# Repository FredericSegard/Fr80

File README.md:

# Fr80

 ## Z80 Homebrew computer, code-named Fr80, pronounced Freddy.
This repo will contain all the elements for a complete Z80 system (Work in progress)

### The Backplane:
The goal is to first make a ubiquitous backplane that could accommodate many 8 or 16-bit architectures, including most x86 that is compatible, Z80, eZ80, z8000, 65C02, 65C816, 6809... You name it, it should handle it. The only difference is in the PCB labeling. I have labeled the breadboard header as per the PC ISA standard on row 1, row 2 is for the Z80, and row 3 is for the 65C02. The breadboard pins are pin-to-pin mapped A1-A13 on the left, and B1-B31 on the right.
 
This backplane follows the ISA power rail standard. This means the +5, ground, +12V, and -12V lanes are where they should be. However, there is provision for a -5V regulator, since most ATX PSUs no longer support it. And since 3.3V is more prevalent these days, I have assigned the -5V lane to +3.3V. However, you can select which voltage you need by simply changing a jumper's position. There is an alternate barrel jack power input for 5 volts only. There is a provision for a 3.3V regulator should you need it. Both power sources are soft power-on. Jumpers are present to repurpose the button, since electrically, they could not be tied together.

It is a passive backplane, so there should be no interference with other signal types. So in theory, you could reassign all non-power rail buses, except for the reset lane and A7 and A8. The reset circuit, which is jumper selectable between active high or active low, cannot be reassigned. And the CPU activity LED, which monitors A7 or A8 (jumper selectable), can't also be moved.

I have just received the PCBs from the fab house. I will assemble it and let you know if everything works as intended.

.jpg?raw=true)

### The Core CPU card:
I made several iterations of the CPU board, but now I'm satisfied with this revision 3. It's a very compact 100mm² 4-layer board, that contains the CPU, 128KB Flash, 512KM RAM, bank switching circuitry, a priority interrupt encoder, a CTC, and an SIO with USB ports (type A and type B).

I gave myself a challenge to fit as much as possible in a 100mm² PCB, all the while managing to put in a ZIF socket and some blinkenlights. The board is so stuffed with components, that I needed to place the bypass capacitors in the sockets, as well as some resistors. 

I will send out the Gerber for manufacturing, and keep you posted.

/Docs%20and%20Images/Front%20with%20components.jpg?raw=true)

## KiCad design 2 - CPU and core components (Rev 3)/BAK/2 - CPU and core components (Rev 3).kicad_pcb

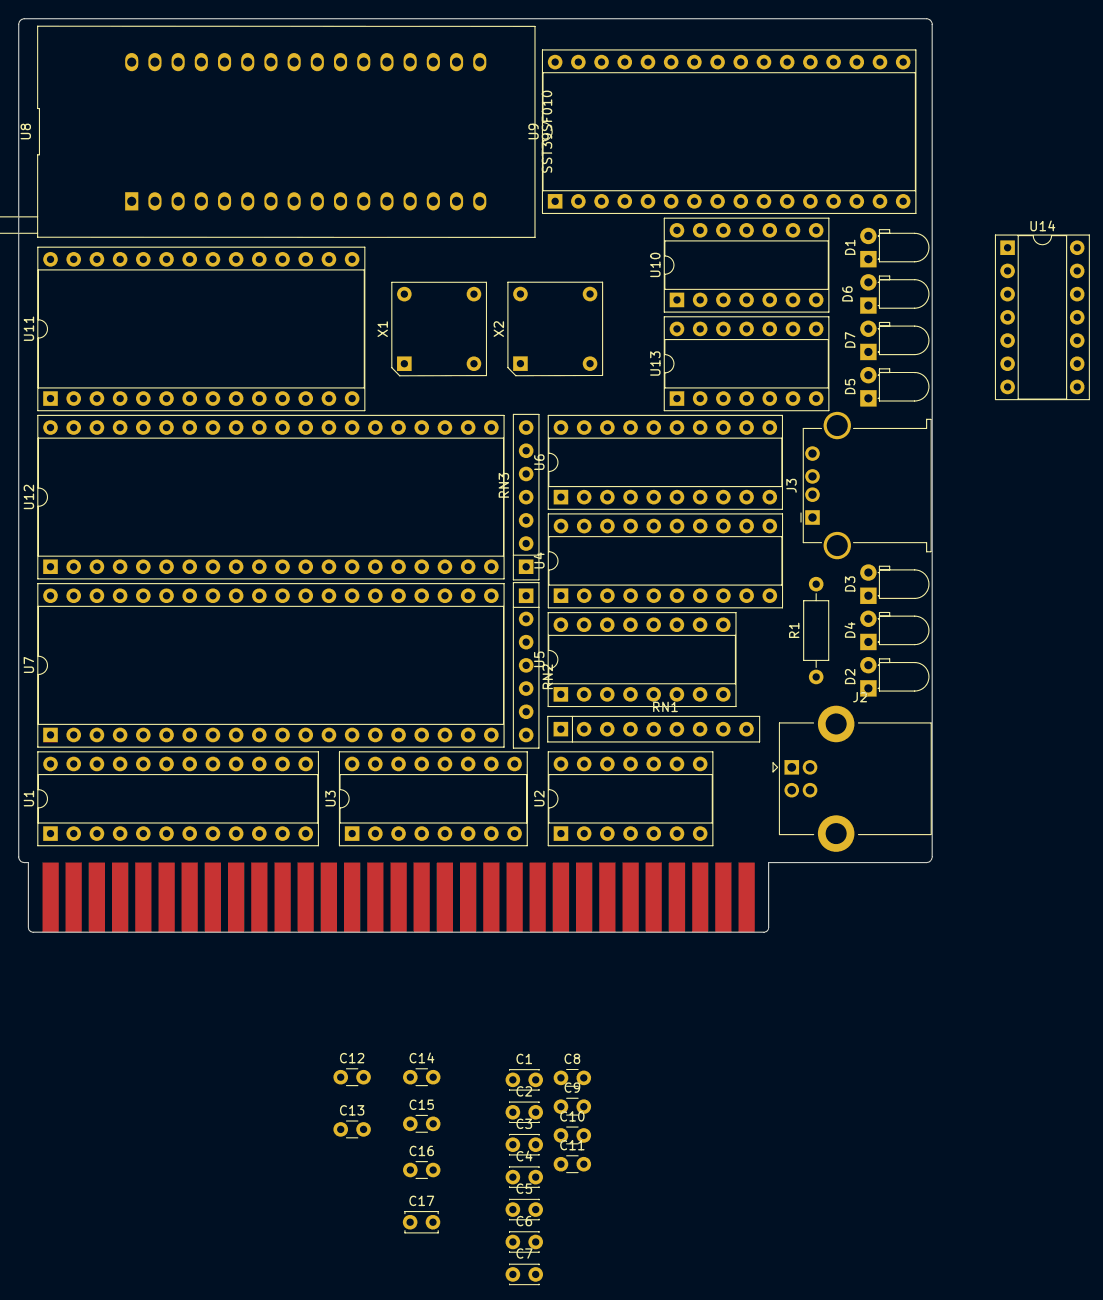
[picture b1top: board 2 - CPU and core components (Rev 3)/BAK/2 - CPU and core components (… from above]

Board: 2 copper layers, 100.0 x 100.0 mm, 47 parts (0 on the bottom side), 95 nets, no tracks yet.

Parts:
C1, C2, C3, C4, C5, C6, C7: 1µF; C_Disc_D3.0mm_W2.0mm_P2.50mm
C8, C9, C10, C11, C14, C15, C16: 1µF; C_Disc_D3.0mm_W1.6mm_P2.50mm
C12, C13: 0.47µF; C_Disc_D3.0mm_W1.6mm_P2.50mm
C17: 1µF; C_Disc_D3.4mm_W2.1mm_P2.50mm
D1: STATUS; LED_D3.0mm_Horizontal_O1.27mm_Z2.0mm
D2: USB 1; LED_D3.0mm_Horizontal_O1.27mm_Z2.0mm
D3: TX 1; LED_D3.0mm_Horizontal_O1.27mm_Z2.0mm
D4: RX 1; LED_D3.0mm_Horizontal_O1.27mm_Z2.0mm
D5: USB 2; LED_D3.0mm_Horizontal_O1.27mm_Z2.0mm
D6: TX 2; LED_D3.0mm_Horizontal_O1.27mm_Z2.0mm
D7: RX 2; LED_D3.0mm_Horizontal_O1.27mm_Z2.0mm
J1: CARD EDGE; BUS_XT v2
J2: COM 1; USB_B_Lumberg_2411_02_Horizontal
J3: COM 2; USB_A_Stewart_SS-52100-001_Horizontal
R1: 3K3; R_Axial_DIN0207_L6.3mm_D2.5mm_P10.16mm_Horizontal
RN1: 3K3; R_Array_SIP9
RN2, RN3: 3K3; R_Array_SIP7
U1: ATF22V10C; DIP-24_W7.62mm_Socket
U2: 74HCT32; DIP-14_W7.62mm_Socket
U3: 74LS174; DIP-16_W7.62mm_Socket
U4: 74HCT541; DIP-20_W7.62mm_Socket
U5: 74HCT148; DIP-16_W7.62mm_Socket
U6: 74HCT573; DIP-20_W7.62mm_Socket
U7: Z84C0010; DIP-40_W15.24mm_Socket
U8: SST39SF010; ZIF_Socket-32
U9: AS6C4008; DIP-32_W15.24mm_Socket
U10: 74HCT30; DIP-14_W7.62mm_Socket
U11: Z84C3010; DIP-28_W15.24mm_Socket
U12: Z84C4010; DIP-40_W15.24mm_Socket
U13, U14: MCP2221A; DIP-14_W7.62mm_Socket
X1: 10 MHz; DIP-8-4_W7.62mm_Oscillator_Socket
X2: 3.6864 MHz; DIP-8-4_W7.62mm_Oscillator_Socket

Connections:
+5V: C1.1, C2.1, C3.1, C4.1, C5.1, C6.1, C7.1, C8.1, C9.1, C10.1, C11.1, C14.1, C15.1, C16.1, C17.1, J1.34 (B3), J1.60 (B29), RN1.1 (common), RN2.1 (common), RN3.1 (common), U1.24 (VCC), U2.14 (VCC), U3.16 (VCC), U4.20 (VCC), U5.16 (VCC), U6.20 (VCC), U7.11 (VCC), U8.32 (VCC), U9.32 (VCC), U10.14 (VCC), U11.24 (VCC), U12.9 (VCC), U13.1 (VCC), U14.1 (VCC), X1.1 (EN), X1.8 (Vcc), X2.1 (EN), X2.8 (Vcc)
/CTC & SIO/D1+: J2.3 (D+), U13.13 (D+)
/CTC & SIO/D1-: J2.2 (D-), U13.12 (D-)
/CTC & SIO/D2+: J3.3 (D+), U14.13 (D+)
/CTC & SIO/D2-: J3.2 (D-), U14.12 (D-)
/GND: J1.32 (B1), J1.41 (B10), J1.62 (B31)
/Glue Logic/RBA15: U2.2, U3.2 (Q0), U4.2 (A0)
/Glue Logic/RBA16: U2.5, U3.5 (Q1), U4.3 (A1)
/Glue Logic/RBA17: U2.10, U3.7 (Q2), U4.4 (A2)
/Glue Logic/RBA18: U2.13, U3.10 (Q3), U4.5 (A3)
A0: J1.31 (A31), U7.30 (A0), U8.12 (A0), U9.12 (A0), U11.18 (CS0), U12.34 (B/~A)
A1: J1.30 (A30), U7.31 (A1), U8.11 (A1), U9.11 (A1), U11.19 (CS1), U12.33 (C/~D)
A2: J1.29 (A29), U1.7 (I), U7.32 (A2), U8.10 (A2), U9.10 (A2)
A3: J1.28 (A28), U1.8 (I), U7.33 (A3), U8.9 (A3), U9.9 (A3)
A4: J1.27 (A27), U1.9 (I), U7.34 (A4), U8.8 (A4), U9.8 (A4)
A5: J1.26 (A26), U1.10 (I), U7.35 (A5), U8.7 (A5), U9.7 (A5)
A6: J1.25 (A25), U1.11 (I), U7.36 (A6), U8.6 (A6), U9.6 (A6)
A7: J1.24 (A24), U1.13 (I), U7.37 (A7), U8.5 (A7), U9.5 (A7)
A8: J1.23 (A23), U7.38 (A8), U8.27 (A8), U9.27 (A8)
A9: J1.22 (A22), U7.39 (A9), U8.26 (A9), U9.26 (A9)
A10: J1.21 (A21), U7.40 (A10), U8.23 (A10), U9.23 (A10)
A11: J1.20 (A20), U7.1 (A11), U8.25 (A11), U9.25 (A11)
A12: J1.19 (A19), U7.2 (A12), U8.4 (A12), U9.4 (A12)
A13: J1.18 (A18), U7.3 (A13), U8.28 (A13), U9.28 (A13)
A14: J1.17 (A17), U7.4 (A14), U8.29 (A14), U9.3 (A14)
A15: J1.16 (A16), U2.1, U2.4, U2.9, U2.12, U7.5 (A15), U8.3 (A15)
BA15: U2.3, U9.31 (A15)
BA16: U2.6, U9.2 (A16)
BA17: U2.8, U9.30 (A17)
BA18: U2.11, U9.1 (A18)
BUS_IEO: J1.15 (A15), RN2.6 (R5), U12.6 (IEI)
CLK: J1.51 (B20), U7.6 (CLK), U11.15 (CLK), U12.20 (CLK), X1.5 (OUT)
CLK2: J1.39 (B8), U11.21 (CLK/TRG2), U11.22 (CLK/TRG1), U11.23 (CLK/TRG0), U12.13 (~RxCA), U12.14 (~TxCA), U12.27 (~RxTxCB), X2.5 (OUT)
CTCLK: J1.14 (A14), U11.8 (ZC/TO1)
CTC_IEI: RN2.7 (R6), U11.13 (IEI), U12.7 (IEO)
D0: J1.9 (A9), U3.3 (D0), U4.18 (Y0), U6.19 (Q0), U7.14 (D0), U8.13 (DQ0), U9.13 (DQ0), U11.25 (D0), U12.40 (D0)
D1: J1.8 (A8), U3.4 (D1), U4.17 (Y1), U6.18 (Q1), U7.15 (D1), U8.14 (DQ1), U9.14 (DQ1), U11.26 (D1), U12.1 (D1)
D2: J1.7 (A7), U3.6 (D2), U4.16 (Y2), U6.17 (Q2), U7.12 (D2), U8.15 (DQ2), U9.15 (DQ2), U11.27 (D2), U12.39 (D2)
D3: J1.6 (A6), U3.11 (D3), U4.15 (Y3), U6.16 (Q3), U7.8 (D3), U8.17 (DQ3), U9.17 (DQ3), U11.28 (D3), U12.2 (D3)
D4: J1.5 (A5), U4.14 (Y4), U6.15 (Q4), U7.7 (D4), U8.18 (DQ4), U9.18 (DQ4), U11.1 (D4), U12.38 (D4)
D5: J1.4 (A4), U4.13 (Y5), U6.14 (Q5), U7.9 (D5), U8.19 (DQ5), U9.19 (DQ5), U11.2 (D5), U12.3 (D5)
D6: J1.3 (A3), U4.12 (Y6), U6.13 (Q6), U7.10 (D6), U8.20 (DQ6), U9.20 (DQ6), U11.3 (D6), U12.37 (D6)
D7: J1.2 (A2), U4.11 (Y7), U6.12 (Q7), U7.13 (D7), U8.21 (DQ7), U9.21 (DQ7), U11.4 (D7), U12.4 (D7)
GND: C1.2, C2.2, C3.2, C4.2, C5.2, C6.2, C7.2, C8.2, C9.2, C10.2, C11.2, C12.2, C13.2, C14.2, C15.2, C16.2, C17.2, D1.1 (K), J2.4 (GND), J2.5 (Shield), J3.4 (GND), J3.5 (Shield), U1.12 (GND), U2.7 (GND), U3.8 (GND), U3.13 (D4), U3.14 (D5), U4.6 (A4), U4.7 (A5), U4.8 (A6), U4.9 (A7), U4.10 (GND), U5.5 (EI), U5.8 (GND), U6.2 (D0), U6.6 (D4), U6.7 (D5), U6.8 (D6), U6.9 (D7), U6.10 (GND), U7.29 (GND), U8.1 (NC), U8.2 (A16), U8.16 (GND), U8.30 (NC), U9.16 (GND), U10.7 (GND), U11.5 (GND), U12.18 (~CTSA), U12.19 (~DCDA), U12.22 (~DCDB), U12.23 (~CTSB), U12.31 (GND), U13.14 (GND), U14.14 (GND), X1.4 (GND), X2.4 (GND)
MODE2: U1.14 (I/O), U6.1 (OE)
unnamed: D1.2 (A), R1.2
unnamed: D2.2 (A), RN3.4 (R3)
unnamed: D2.1 (K), U13.7 (GP2_(USB))
unnamed: D3.2 (A), RN3.3 (R2)
unnamed: D3.1 (K), U13.3 (GP1_(Tx))
unnamed: D4.2 (A), RN3.2 (R1)
unnamed: D4.1 (K), U13.2 (GP0_(Rx))
unnamed: D5.2 (A), RN3.5 (R4)
unnamed: D5.1 (K), U14.7 (GP2_(USB))
unnamed: D6.2 (A), RN3.6 (R5)
unnamed: D6.1 (K), U14.3 (GP1_(Tx))
unnamed: D7.2 (A), RN3.7 (R6)
unnamed: D7.1 (K), U14.2 (GP0_(Rx))
unnamed: R1.1, U10.8
unnamed: U5.9 (S0), U6.3 (D1)
unnamed: U5.7 (S1), U6.4 (D2)
unnamed: U5.6 (S2), U6.5 (D3)
unnamed: U11.7 (ZC/TO0), U11.20 (CLK/TRG3)
unnamed: U12.12 (RxDA), U13.6 (Tx_Out)
unnamed: U12.28 (RxDB), U14.6 (Tx_Out)
unnamed: U12.15 (TxDA), U13.5 (Rx_In)
unnamed: U12.26 (TxDB), U14.5 (Rx_In)
unnamed: C12.1, U13.11 (VUSB)
unnamed: C13.1, U14.11 (VUSB)
~BANK_RD: U1.17 (I/O), U4.1 (G1), U4.19 (G2)
~BANK_WR: U1.18 (I/O), U3.9 (Cp)
~BUSAK: J1.48 (B17), U7.23 (~BUSAK), U10.11
~BUSRQ: J1.47 (B16), RN2.2 (R1), U7.25 (~BUSRQ), U10.6
~CTC_CS: U1.15 (I/O), U11.16 (~CE)
~HALT: J1.50 (B19), U7.18 (~HALT), U10.2
~INT: RN2.3 (R2), U5.14 (GS), U7.16 (~INT), U10.4
~IORQ: J1.43 (B12), U1.3 (I), U7.20 (~IORQ), U11.10 (~IORQ), U12.36 (~IORQ)
~IRQ0: J1.59 (B28), RN1.7 (R6), U5.4 (I7), U11.12 (~INT)
~IRQ1: J1.58 (B27), RN1.5 (R4), U5.3 (I6)
~IRQ2: J1.35 (B4), RN1.3 (R2), U5.2 (I5)
~IRQ3: J1.56 (B25), RN1.2 (R1), U5.1 (I4), U12.5 (~INT)
~IRQ4: J1.55 (B24), RN1.4 (R3), U5.13 (I3)
~IRQ5: J1.54 (B23), RN1.6 (R5), U5.12 (I2)
~IRQ6: J1.53 (B22), RN1.8 (R7), U5.11 (I1)
~IRQ7: J1.52 (B21), RN1.9 (R8), U5.10 (IO)
~M1: J1.37 (B6), U1.6 (I), U6.11 (Load), U7.27 (~M1), U11.14 (~M1), U12.8 (~M1)
~MREQ: J1.42 (B11), U1.2 (I), U7.19 (~MREQ), U9.22 (~CS)
~NMI: J1.57 (B26), RN2.5 (R4), U7.17 (~NMI), U10.5
~RAM_OE: U1.19 (I/O), U9.24 (~OE)
~RD: J1.44 (B13), U1.5 (I), U7.21 (~RD), U8.24 (~OE), U11.6 (~RD), U12.32 (~RD)
~RESET: J1.33 (B2), U1.1 (I/CLK), U3.1 (~Mr), U7.26 (~RST), U10.12, U11.17 (~RST), U12.21 (~RST)
~ROM_CS: U1.20 (I/O), U8.22 (~CS), U10.1
~SIO_CS: U1.16 (I/O), U12.35 (~CE)
~WAIT: J1.49 (B18), RN2.4 (R3), U7.24 (~WAIT), U10.3
~WR: J1.45 (B14), U1.4 (I/PD), U7.22 (~WR), U8.31 (~PGM), U9.29 (~WE)

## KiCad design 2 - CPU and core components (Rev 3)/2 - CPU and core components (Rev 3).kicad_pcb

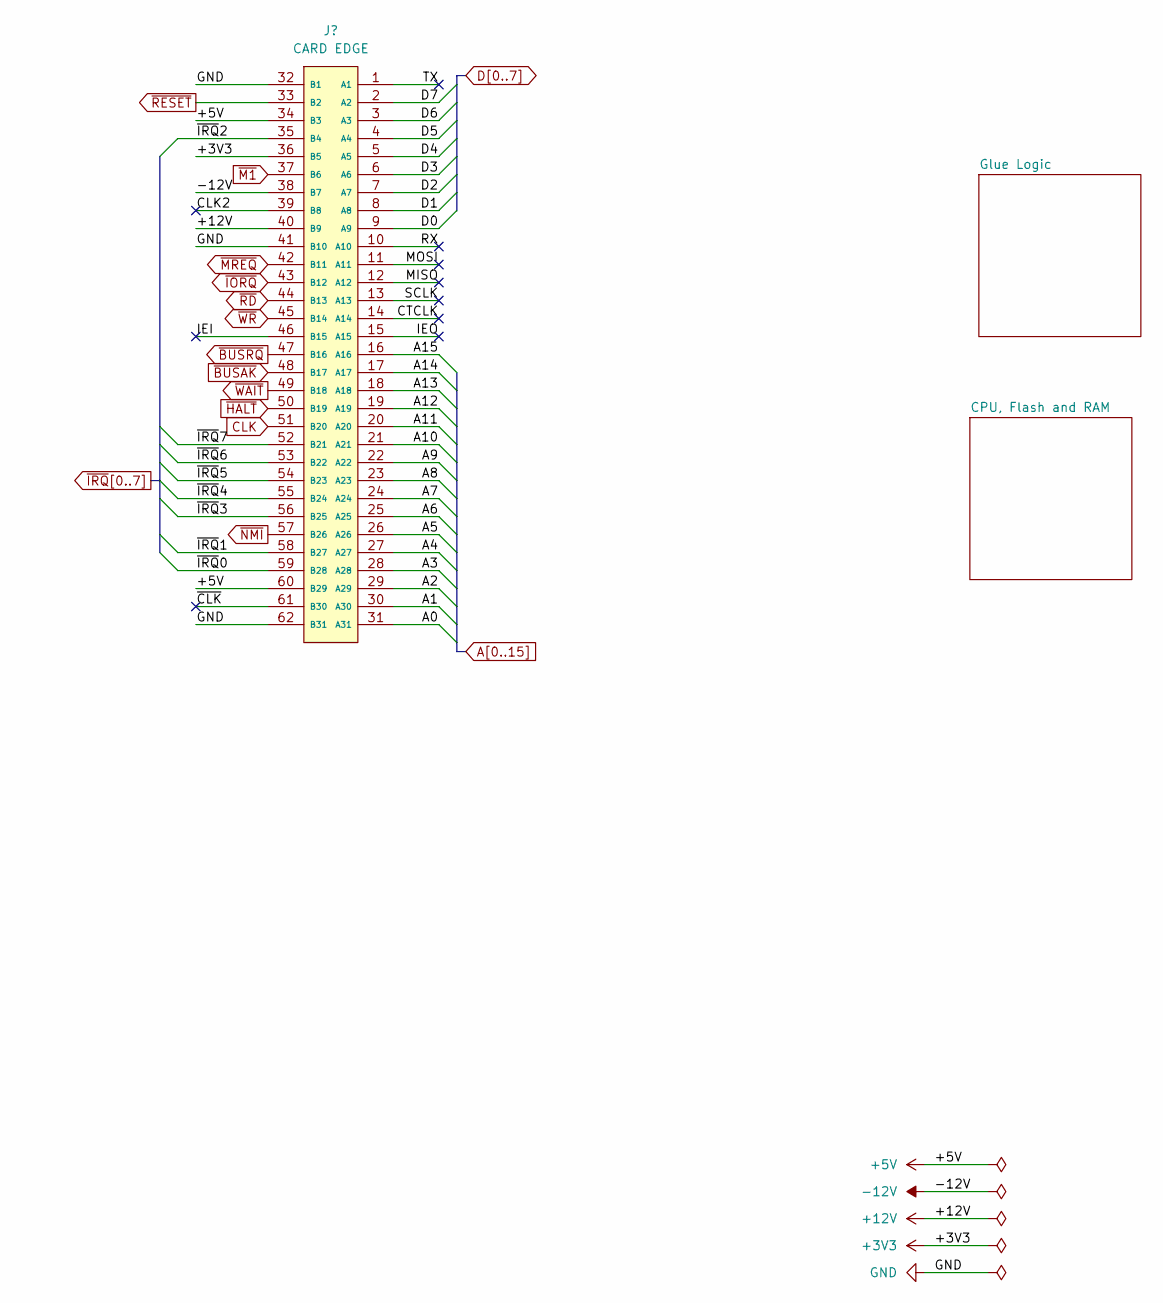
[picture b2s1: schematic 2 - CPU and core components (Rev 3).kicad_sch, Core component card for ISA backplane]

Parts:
J1: CARD EDGE; BUS_XT v2; Mouser Part Number 571-6-5530843-5

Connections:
+3V3: J1.36 (B5)
+5V: J1.34 (B3), J1.60 (B29); also elsewhere on the board
+12V: J1.40 (B9)
-12V: J1.38 (B7)
/CLK2: J1.39 (B8)
/CTCLK: J1.14 (A14)
/IEI: J1.46 (B15)
/IEO: J1.15 (A15)
/MISO: J1.12 (A12)
/MOSI: J1.11 (A11)
/RX: J1.10 (A10)
/SCLK: J1.13 (A13)
/TX: J1.1 (A1)
/~CLK: J1.61 (B30)
A0: J1.31 (A31); also elsewhere on the board
A1: J1.30 (A30); also elsewhere on the board
A2: J1.29 (A29); also elsewhere on the board
A3: J1.28 (A28); also elsewhere on the board
A4: J1.27 (A27); also elsewhere on the board
A5: J1.26 (A26); also elsewhere on the board
A6: J1.25 (A25); also elsewhere on the board
A7: J1.24 (A24); also elsewhere on the board
A8: J1.23 (A23); also elsewhere on the board
A9: J1.22 (A22); also elsewhere on the board
A10: J1.21 (A21); also elsewhere on the board
A11: J1.20 (A20); also elsewhere on the board
A12: J1.19 (A19); also elsewhere on the board
A13: J1.18 (A18); also elsewhere on the board
A14: J1.17 (A17); also elsewhere on the board
A15: J1.16 (A16); also elsewhere on the board
CLK: J1.51 (B20); also elsewhere on the board
D0: J1.9 (A9); also elsewhere on the board
D1: J1.8 (A8); also elsewhere on the board
D2: J1.7 (A7); also elsewhere on the board
D3: J1.6 (A6); also elsewhere on the board
D4: J1.5 (A5); also elsewhere on the board
D5: J1.4 (A4); also elsewhere on the board
D6: J1.3 (A3); also elsewhere on the board
D7: J1.2 (A2); also elsewhere on the board
GND: J1.32 (B1), J1.41 (B10), J1.62 (B31); also elsewhere on the board
~BUSAK: J1.48 (B17); also elsewhere on the board
~BUSRQ: J1.47 (B16); also elsewhere on the board
~HALT: J1.50 (B19); also elsewhere on the board
~IORQ: J1.43 (B12); also elsewhere on the board
~IRQ0: J1.59 (B28); also elsewhere on the board
~IRQ1: J1.58 (B27); also elsewhere on the board
~IRQ2: J1.35 (B4); also elsewhere on the board
~IRQ3: J1.56 (B25); also elsewhere on the board
~IRQ4: J1.55 (B24); also elsewhere on the board
~IRQ5: J1.54 (B23); also elsewhere on the board
~IRQ6: J1.53 (B22); also elsewhere on the board
~IRQ7: J1.52 (B21); also elsewhere on the board
~M1: J1.37 (B6); also elsewhere on the board
~MREQ: J1.42 (B11); also elsewhere on the board
~NMI: J1.57 (B26); also elsewhere on the board
~RD: J1.44 (B13); also elsewhere on the board
~RESET: J1.33 (B2); also elsewhere on the board
~WAIT: J1.49 (B18); also elsewhere on the board
~WR: J1.45 (B14); also elsewhere on the board

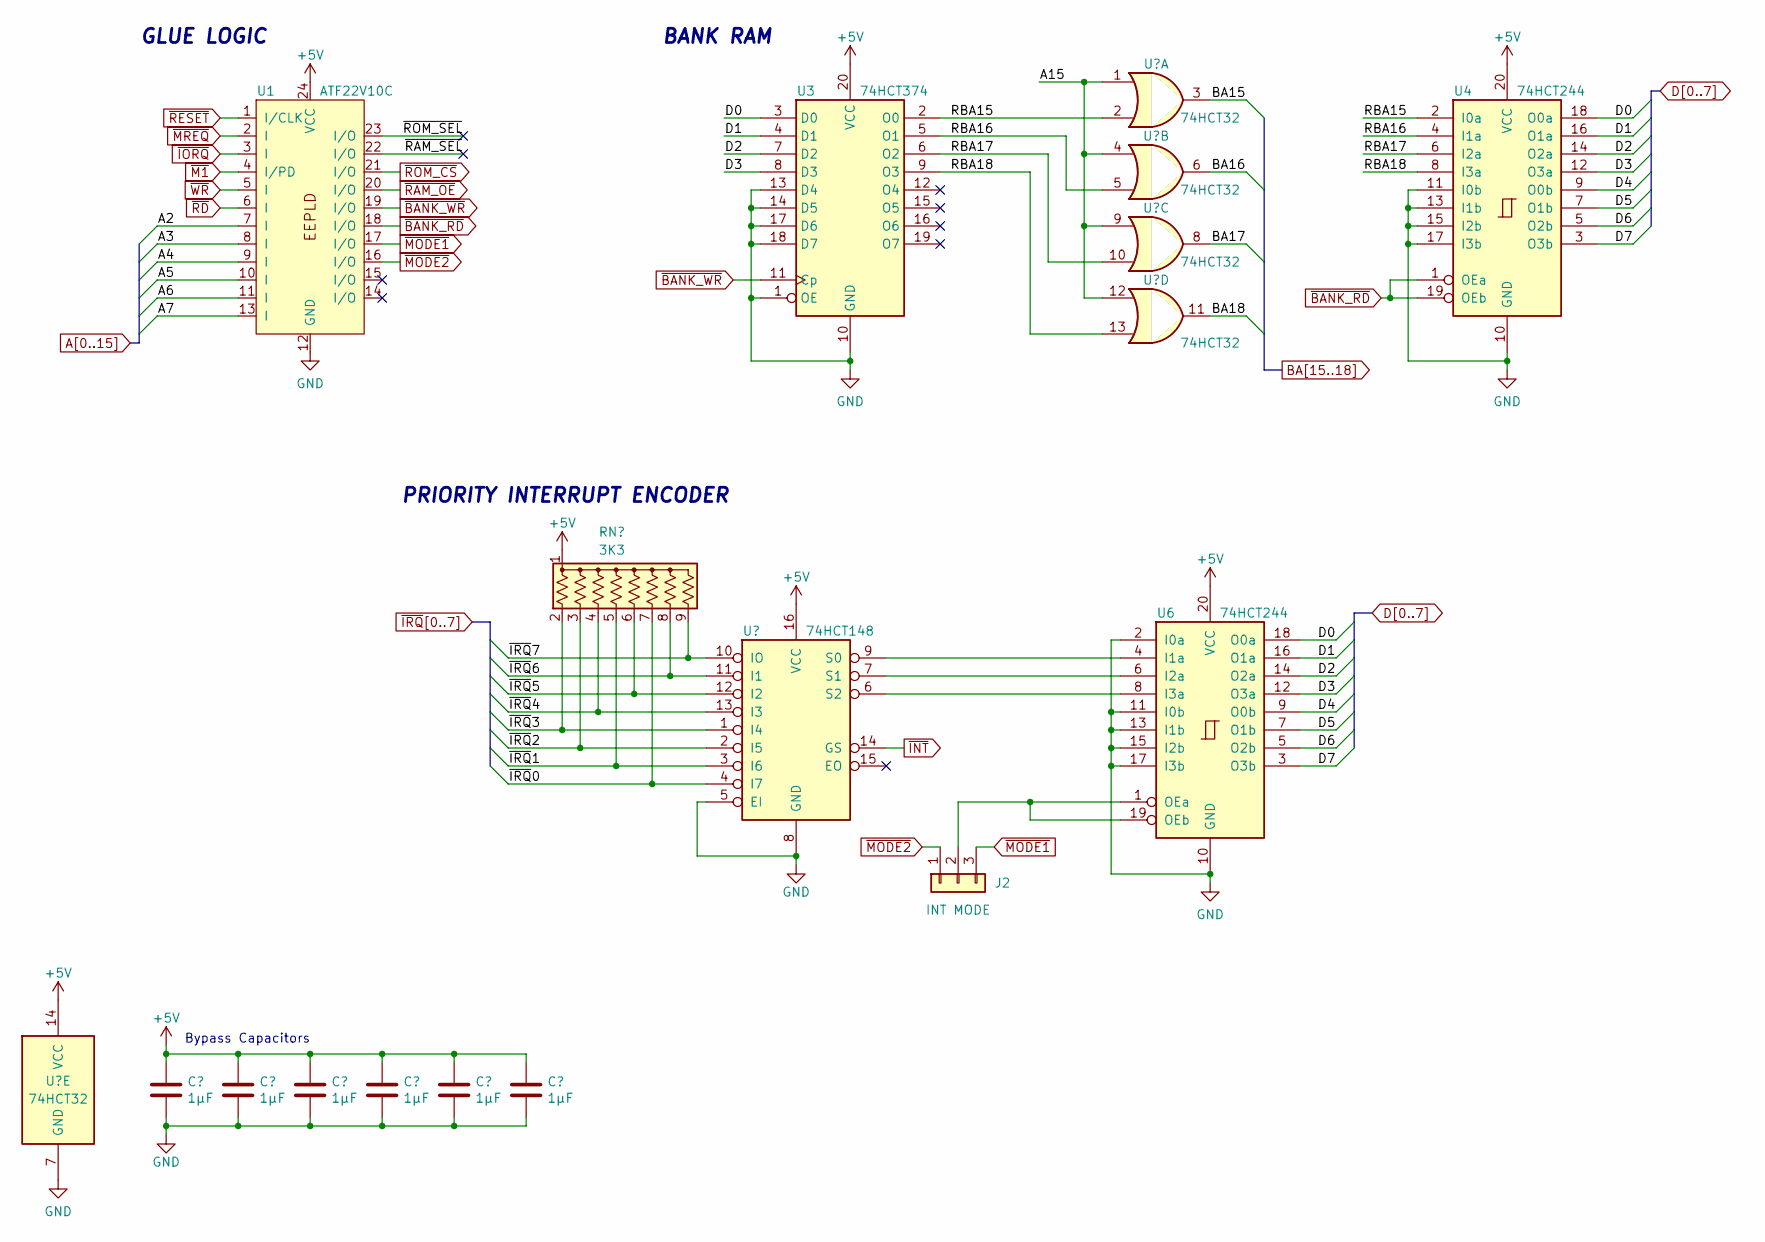
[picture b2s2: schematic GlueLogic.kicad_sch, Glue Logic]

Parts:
C1, C2, C3, C5: 1µF; C_Disc_D3.0mm_W1.6mm_P2.50mm
C4, C6: 1µF; C_Disc_D3.0mm_W2.0mm_P2.50mm
J2: INT MODE; PinHeader_1x03_P2.54mm_Vertical
RN1: 3K3; R_Array_SIP9
U1: ATF22V10C; DIP-24_W7.62mm_Socket
U2: 74HCT32; DIP-14_W7.62mm_Socket
U3: 74HCT374; DIP-20_W7.62mm_Socket
U4, U6: 74HCT244; DIP-20_W7.62mm_Socket
U5: 74HCT148; DIP-16_W7.62mm_Socket

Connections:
+5V: C1.1, C2.1, C3.1, C4.1, C5.1, C6.1, RN1.1 (common), U1.24 (VCC), U2.14 (VCC), U3.20 (VCC), U4.20 (VCC), U5.16 (VCC), U6.20 (VCC); also elsewhere on the board
/Glue Logic/RBA15: U2.2, U3.2 (O0), U4.2 (I0a)
/Glue Logic/RBA16: U2.5, U3.5 (O1), U4.4 (I1a)
/Glue Logic/RBA17: U2.10, U3.6 (O2), U4.6 (I2a)
/Glue Logic/RBA18: U2.13, U3.9 (O3), U4.8 (I3a)
/Glue Logic/~RAM_SEL: U1.22 (I/O)
/Glue Logic/~ROM_SEL: U1.23 (I/O)
A2: U1.7 (I); also elsewhere on the board
A3: U1.8 (I); also elsewhere on the board
A4: U1.9 (I); also elsewhere on the board
A5: U1.10 (I); also elsewhere on the board
A6: U1.11 (I); also elsewhere on the board
A7: U1.13 (I); also elsewhere on the board
A15: U2.1, U2.4, U2.9, U2.12; also elsewhere on the board
BA15: U2.3; also elsewhere on the board
BA16: U2.6; also elsewhere on the board
BA17: U2.8; also elsewhere on the board
BA18: U2.11; also elsewhere on the board
D0: U3.3 (D0), U4.18 (O0a), U6.18 (O0a); also elsewhere on the board
D1: U3.4 (D1), U4.16 (O1a), U6.16 (O1a); also elsewhere on the board
D2: U3.7 (D2), U4.14 (O2a), U6.14 (O2a); also elsewhere on the board
D3: U3.8 (D3), U4.12 (O3a), U6.12 (O3a); also elsewhere on the board
D4: U4.9 (O0b), U6.9 (O0b); also elsewhere on the board
D5: U4.7 (O1b), U6.7 (O1b); also elsewhere on the board
D6: U4.5 (O2b), U6.5 (O2b); also elsewhere on the board
D7: U4.3 (O3b), U6.3 (O3b); also elsewhere on the board
GND: C1.2, C2.2, C3.2, C4.2, C5.2, C6.2, U1.12 (GND), U2.7 (GND), U3.1 (OE), U3.10 (GND), U3.13 (D4), U3.14 (D5), U3.17 (D6), U3.18 (D7), U4.10 (GND), U4.11 (I0b), U4.13 (I1b), U4.15 (I2b), U4.17 (I3b), U5.5 (EI), U5.8 (GND), U6.2 (I0a), U6.10 (GND), U6.11 (I0b), U6.13 (I1b), U6.15 (I2b), U6.17 (I3b); also elsewhere on the board
unnamed: J2.2, U6.1 (OEa), U6.19 (OEb)
unnamed: U5.9 (S0), U6.4 (I1a)
unnamed: U5.7 (S1), U6.6 (I2a)
unnamed: U5.6 (S2), U6.8 (I3a)
~BANK_RD: U1.18 (I/O), U4.1 (OEa), U4.19 (OEb)
~BANK_WR: U1.19 (I/O), U3.11 (Cp)
~INT: U5.14 (GS); also elsewhere on the board
~IORQ: U1.3 (I); also elsewhere on the board
~IRQ0: RN1.7 (R6), U5.4 (I7); also elsewhere on the board
~IRQ1: RN1.5 (R4), U5.3 (I6); also elsewhere on the board
~IRQ2: RN1.3 (R2), U5.2 (I5); also elsewhere on the board
~IRQ3: RN1.2 (R1), U5.1 (I4); also elsewhere on the board
~IRQ4: RN1.4 (R3), U5.13 (I3); also elsewhere on the board
~IRQ5: RN1.6 (R5), U5.12 (I2); also elsewhere on the board
~IRQ6: RN1.8 (R7), U5.11 (I1); also elsewhere on the board
~IRQ7: RN1.9 (R8), U5.10 (IO); also elsewhere on the board
~M1: U1.4 (I/PD); also elsewhere on the board
~MODE1: J2.3, U1.17 (I/O)
~MODE2: J2.1, U1.16 (I/O)
~MREQ: U1.2 (I); also elsewhere on the board
~RAM_OE: U1.20 (I/O); also elsewhere on the board
~RD: U1.6 (I); also elsewhere on the board
~RESET: U1.1 (I/CLK); also elsewhere on the board
~ROM_CS: U1.21 (I/O); also elsewhere on the board
~WR: U1.5 (I); also elsewhere on the board

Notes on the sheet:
Bypass Capacitors
GLUE LOGIC
BANK RAM
PRIORITY INTERRUPT ENCODER

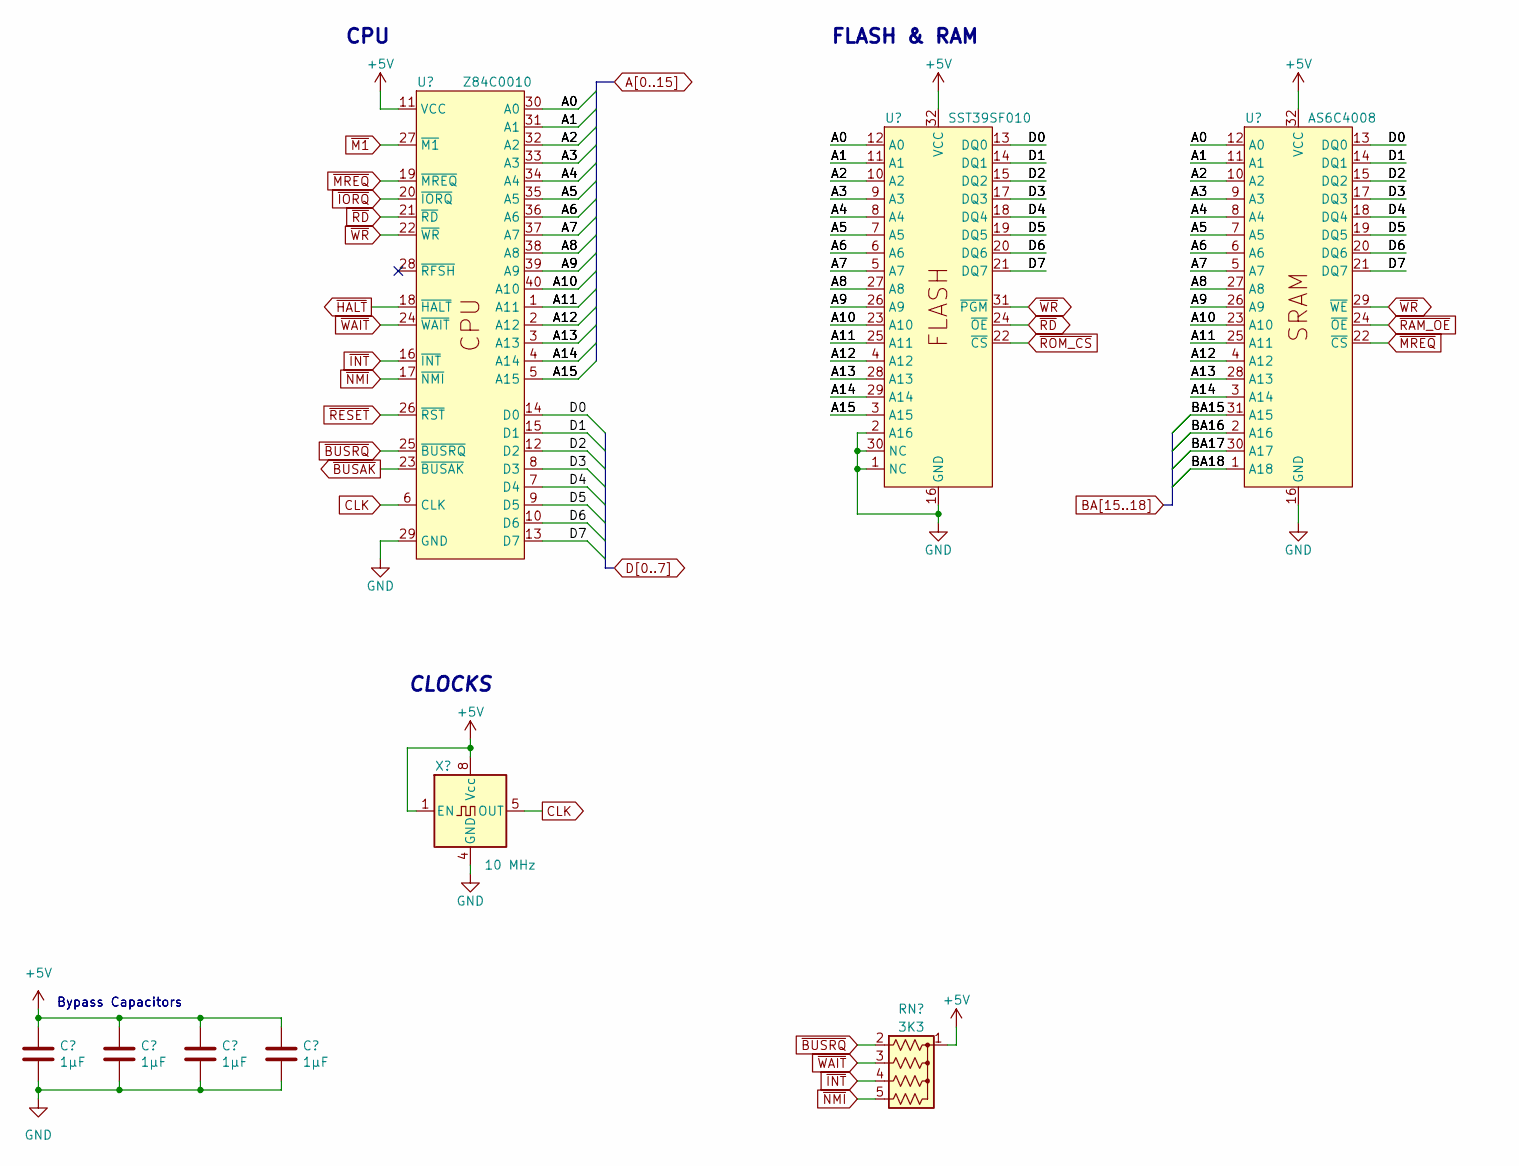
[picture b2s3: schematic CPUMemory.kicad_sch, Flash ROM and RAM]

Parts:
C7, C8, C9, C10: 1µF; C_Disc_D3.4mm_W2.1mm_P2.50mm
RN2: 3K3; R_Array_SIP5
U7: Z84C0010; DIP-40_W15.24mm_Socket
U8: SST39SF010; DIP-32_W15.24mm_Socket
U9: AS6C4008; DIP-32_W15.24mm_Socket
X1: 10 MHz; DIP-8-4_W7.62mm_Oscillator_Socket

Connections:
+5V: C7.1, C8.1, C9.1, C10.1, RN2.1 (common), U7.11 (VCC), U8.32 (VCC), U9.32 (VCC), X1.1 (EN), X1.8 (Vcc); also elsewhere on the board
A0: U7.30 (A0), U8.12 (A0), U9.12 (A0); also elsewhere on the board
A1: U7.31 (A1), U8.11 (A1), U9.11 (A1); also elsewhere on the board
A2: U7.32 (A2), U8.10 (A2), U9.10 (A2); also elsewhere on the board
A3: U7.33 (A3), U8.9 (A3), U9.9 (A3); also elsewhere on the board
A4: U7.34 (A4), U8.8 (A4), U9.8 (A4); also elsewhere on the board
A5: U7.35 (A5), U8.7 (A5), U9.7 (A5); also elsewhere on the board
A6: U7.36 (A6), U8.6 (A6), U9.6 (A6); also elsewhere on the board
A7: U7.37 (A7), U8.5 (A7), U9.5 (A7); also elsewhere on the board
A8: U7.38 (A8), U8.27 (A8), U9.27 (A8); also elsewhere on the board
A9: U7.39 (A9), U8.26 (A9), U9.26 (A9); also elsewhere on the board
A10: U7.40 (A10), U8.23 (A10), U9.23 (A10); also elsewhere on the board
A11: U7.1 (A11), U8.25 (A11), U9.25 (A11); also elsewhere on the board
A12: U7.2 (A12), U8.4 (A12), U9.4 (A12); also elsewhere on the board
A13: U7.3 (A13), U8.28 (A13), U9.28 (A13); also elsewhere on the board
A14: U7.4 (A14), U8.29 (A14), U9.3 (A14); also elsewhere on the board
A15: U7.5 (A15), U8.3 (A15); also elsewhere on the board
BA15: U9.31 (A15); also elsewhere on the board
BA16: U9.2 (A16); also elsewhere on the board
BA17: U9.30 (A17); also elsewhere on the board
BA18: U9.1 (A18); also elsewhere on the board
CLK: U7.6 (CLK), X1.5 (OUT); also elsewhere on the board
D0: U7.14 (D0), U8.13 (DQ0), U9.13 (DQ0); also elsewhere on the board
D1: U7.15 (D1), U8.14 (DQ1), U9.14 (DQ1); also elsewhere on the board
D2: U7.12 (D2), U8.15 (DQ2), U9.15 (DQ2); also elsewhere on the board
D3: U7.8 (D3), U8.17 (DQ3), U9.17 (DQ3); also elsewhere on the board
D4: U7.7 (D4), U8.18 (DQ4), U9.18 (DQ4); also elsewhere on the board
D5: U7.9 (D5), U8.19 (DQ5), U9.19 (DQ5); also elsewhere on the board
D6: U7.10 (D6), U8.20 (DQ6), U9.20 (DQ6); also elsewhere on the board
D7: U7.13 (D7), U8.21 (DQ7), U9.21 (DQ7); also elsewhere on the board
GND: C7.2, C8.2, C9.2, C10.2, U7.29 (GND), U8.1 (NC), U8.2 (A16), U8.16 (GND), U8.30 (NC), U9.16 (GND), X1.4 (GND); also elsewhere on the board
~BUSAK: U7.23 (~BUSAK); also elsewhere on the board
~BUSRQ: RN2.2 (R1), U7.25 (~BUSRQ); also elsewhere on the board
~HALT: U7.18 (~HALT); also elsewhere on the board
~INT: RN2.4 (R3), U7.16 (~INT); also elsewhere on the board
~IORQ: U7.20 (~IORQ); also elsewhere on the board
~M1: U7.27 (~M1); also elsewhere on the board
~MREQ: U7.19 (~MREQ), U9.22 (~CS); also elsewhere on the board
~NMI: RN2.5 (R4), U7.17 (~NMI); also elsewhere on the board
~RAM_OE: U9.24 (~OE); also elsewhere on the board
~RD: U7.21 (~RD), U8.24 (~OE); also elsewhere on the board
~RESET: U7.26 (~RST); also elsewhere on the board
~ROM_CS: U8.22 (~CS); also elsewhere on the board
~WAIT: RN2.3 (R2), U7.24 (~WAIT); also elsewhere on the board
~WR: U7.22 (~WR), U8.31 (~PGM), U9.29 (~WE); also elsewhere on the board

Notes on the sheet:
CLOCKS
CPU
Bypass Capacitors
FLASH & RAM

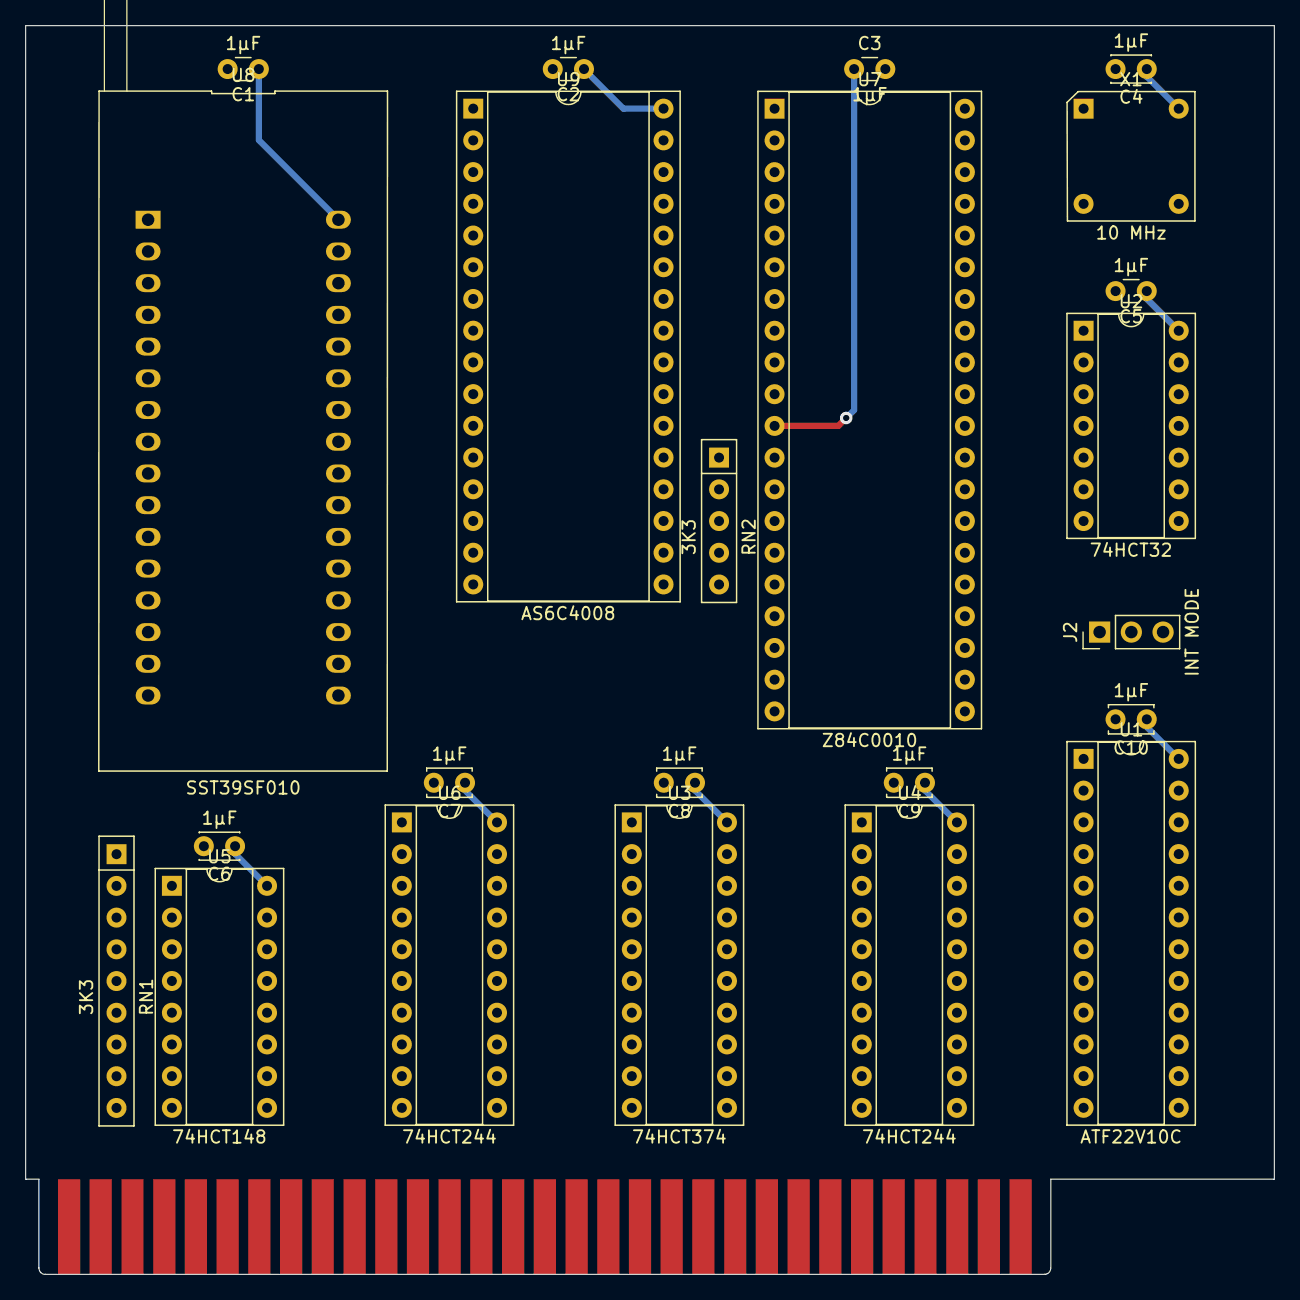
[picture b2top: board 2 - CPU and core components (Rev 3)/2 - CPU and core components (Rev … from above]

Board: 4 copper layers, 100.0 x 100.0 mm, 24 parts (0 on the bottom side), 65 nets.
